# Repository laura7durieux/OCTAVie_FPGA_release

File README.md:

# OCTAVie – Ultrasonic Acquisition Platform

**OCTAVie** is an open-source hardware and software platform designed to capture and analyze ultrasonic vocalizations of animals (up to ≥80 kHz).  
It combines a sensitive microphone module, an analog front-end, an FPGA-based acquisition unit, and a PC application for real-time spectral analysis.

This repository hosts the **complete open-source design files**: electronics, enclosures, FPGA firmware, PC software, documentation, and example datasets.  
The project is developed at **ICube, LNCA, and the Faculty of Physics and Engineering – Strasbourg, France**, within the framework of the **OCTAVie project**.

---

## Quickstart

### 1. Build Hardware
- Go to [hardware/](hardware/)  
- Assemble the **microphone** and the **acquisition unit** following the build guide:  
  - [docs/build_guide/pcb_assembly.md](docs/build_guide/pcb_assembly.md)  
  - [docs/build_guide/mechanical_assembly.md](docs/build_guide/mechanical_assembly.md)  
- Complete system integration: [hardware/system_integration/final_assembly.md](hardware/system_integration/final_assembly.md)

### 2. Program FPGA
- Go to [firmware_fpga/](firmware_fpga/)  
- Compile the project in Quartus (or use provided bitstreams in [releases/](releases/))  
- Load bitstream on Cyclone V GX using Quartus Programmer

### 3. Run PC Application
- Go to [software_pc/](software_pc/)  
- Install dependencies
- Run the software

### Documentation
- Build guide → docs/build_guide/
- User guide → docs/user_guide/user_manual.md
- Validation & tests → docs/validation/
- BOM → docs/publication_assets/tables/bom_master_v1.0.csv

### Citation
If you use this project, please cite the associated HardwareX article and Zenodo DOI:
10.5281/zenodo.17356089

### License
- Hardware → CERN OHL-S v2.0
- Software → GPL-3.0
- Documentation → CC BY-SA 4.0
(see LICENSES/)

---

## Repository Structure
Please see the document : File_list_V1.xlsx 
This document regroups all the documents available in this project as well as their localisation and their status.

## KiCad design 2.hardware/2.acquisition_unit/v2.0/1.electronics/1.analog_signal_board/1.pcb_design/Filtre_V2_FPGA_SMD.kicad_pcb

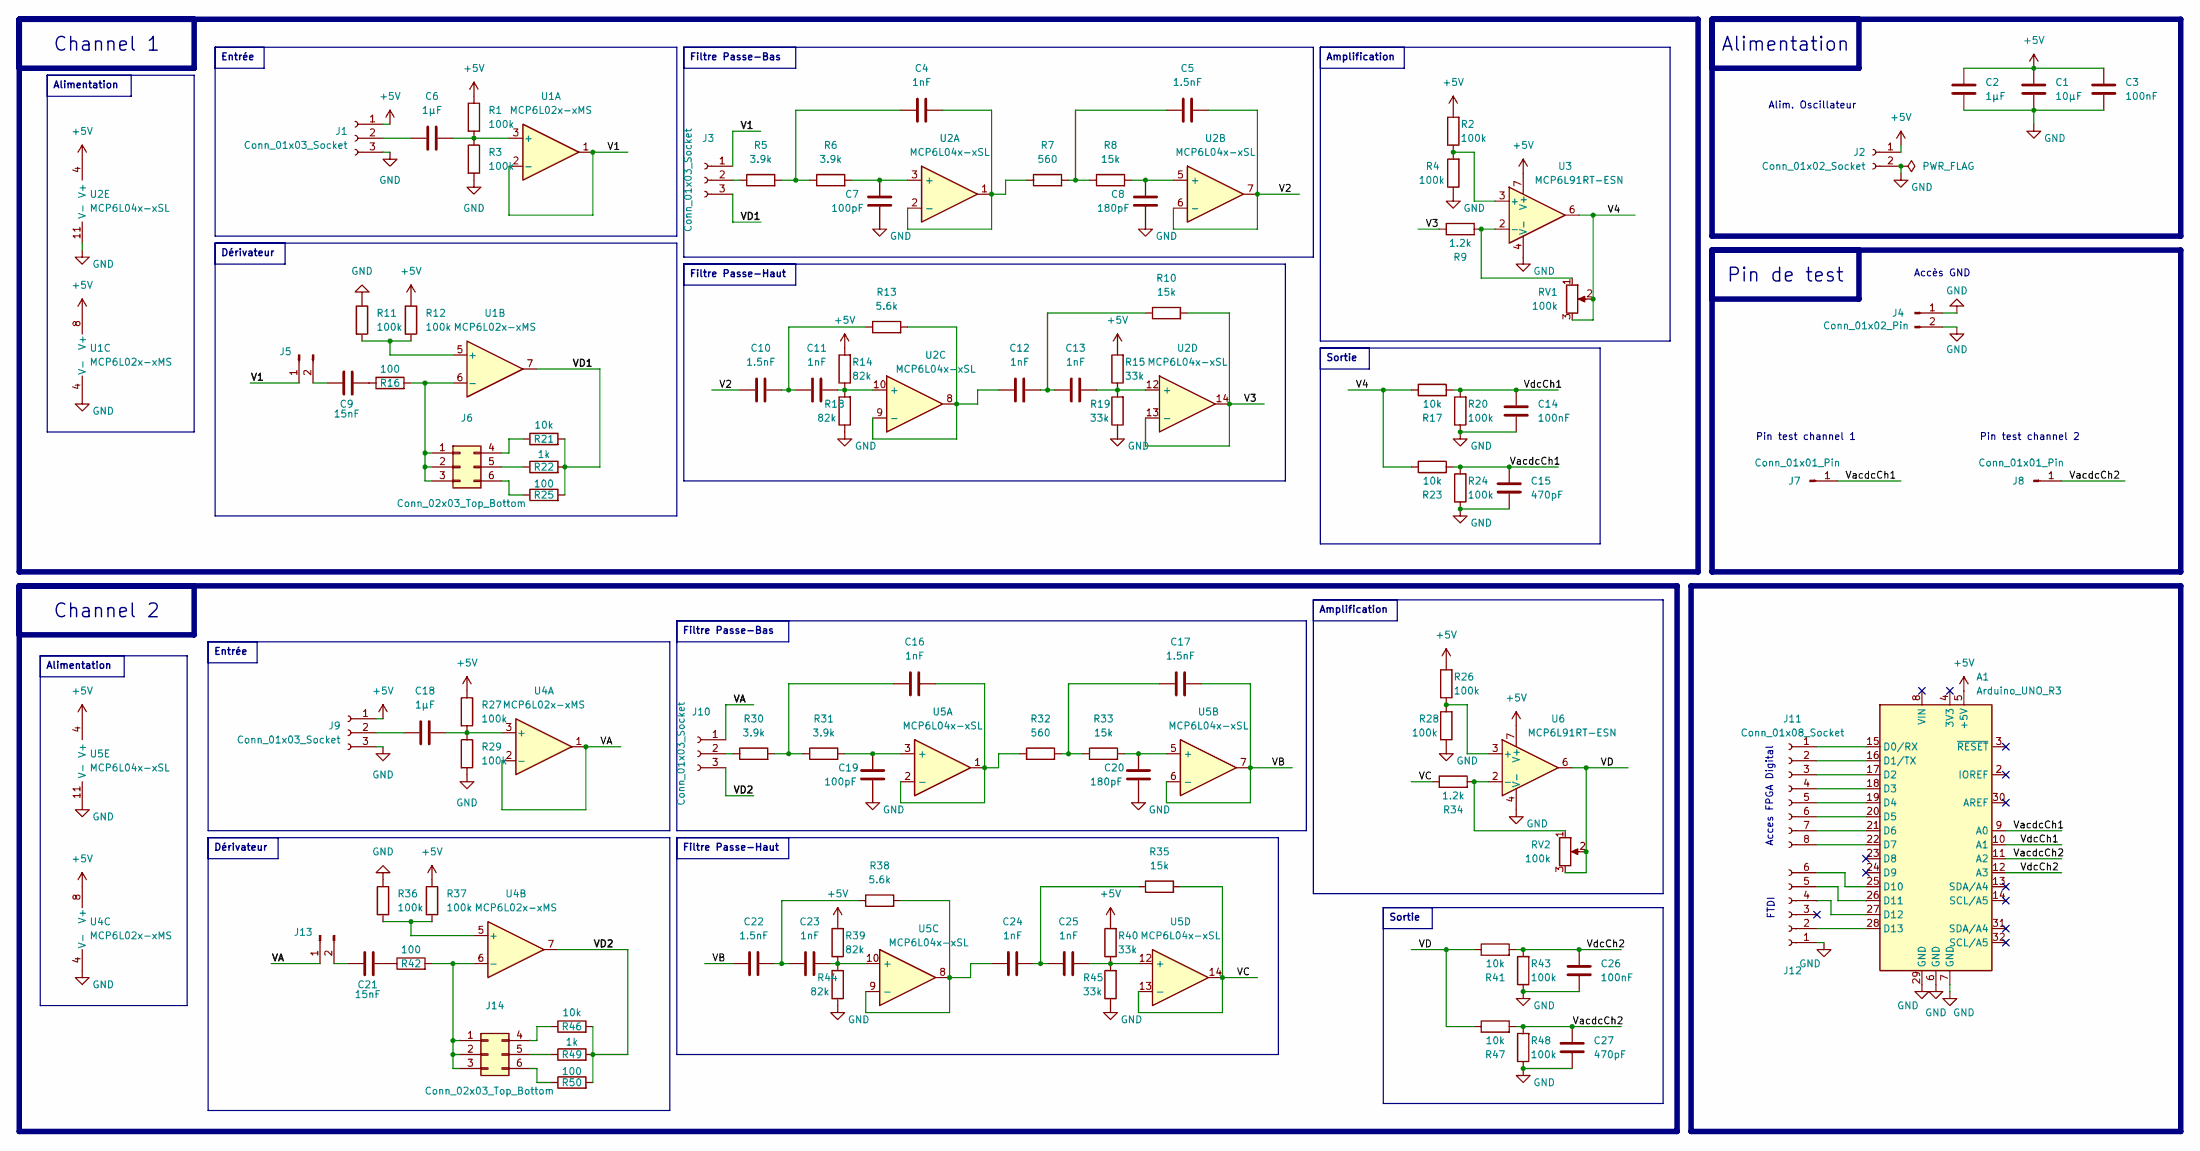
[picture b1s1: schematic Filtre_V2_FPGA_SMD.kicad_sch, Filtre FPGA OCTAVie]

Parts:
A1: Arduino_UNO_R3
C1: 10µF; C_0805_2012Metric; Manufacturer Part Number C0805C106K8PACTU
C2, C6, C18: 1µF; C_0805_2012Metric; Manufacturer Part Number C0805C105K3RAC7800
C3, C14, C26: 100nF; C_0805_2012Metric; Manufacturer Part Number C0805C104M5RAC7800
C4, C11, C12, C13, C16, C23, C24, C25: 1nF; C_0805_2012Metric; Manufacturer Part Number C0805C102K1HAC7800
C5, C10, C17, C22: 1.5nF; C_0805_2012Metric; Manufacturer Part Number C0805C152K3HAC7800
C7, C19: 100pF; C_0805_2012Metric; Manufacturer Part Number C0805C101J5GAC7800
C8, C20: 180pF; C_0805_2012Metric; Manufacturer Part Number C0805C181K5GAC7800
C9, C21: 15nF; C_0805_2012Metric; Manufacturer Part Number C0805C153K5RAC7800
C15, C27: 470pF; C_0805_2012Metric; Manufacturer Part Number C0805C471K5RAC7800
J1, J9: Conn_01x03_Socket; JST_XH_B3B-XH-AM_1x03_P2.50mm_Vertical; Manufacturer Part Number B3B-XH-A
J2: Conn_01x02_Socket; PinHeader_1x02_P2.54mm_Vertical; Manufacturer Part Number PH1-02-UA
J3, J10: Conn_01x03_Socket; PinHeader_1x03_P2.54mm_Vertical; Manufacturer Part Number PH1-03-UA
J4: Conn_01x02_Pin; PinHeader_1x02_P2.54mm_Vertical; Manufacturer Part Number PH1-02-UA
J5, J13: Conn_01x02_Pin; PinSocket_1x02_P2.54mm_Vertical; Manufacturer Part Number PH1-02-UA
J6, J14: Conn_02x03_Top_Bottom; PinHeader_2x03_P2.54mm_Vertical; Manufacturer Part Number PH2-06-UA
J7, J8: Conn_01x01_Pin; PinHeader_1x01_P2.54mm_Vertical; Manufacturer Part Number PH1-01-UA
J11: Conn_01x08_Socket; PinHeader_1x08_P2.54mm_Vertical; Manufacturer Part Number PH1-08-UA
J12: Conn_01x06_Socket; JST_XH_B6B-XH-A_1x06_P2.50mm_Vertical; Manufacturer Part Number B6B-XH-A
R1, R2, R3, R4, R11, R12, R20, R24, R26, R27, R28, R29, R36, R37, R43, R48: 100k; R_0805_2012Metric; Manufacturer Part Number ERJ-P06J104V
R5, R6, R30, R31: 3.9k; R_0805_2012Metric; Manufacturer Part Number ERJ-P06J392V
R7, R32: 560; R_0805_2012Metric; Manufacturer Part Number ERJ-P06J561V
R8, R10, R33, R35: 15k; R_0805_2012Metric; Manufacturer Part Number ERJ-P06J153V
R9, R34: 1.2k; R_0805_2012Metric; Manufacturer Part Number ERJ-P06J122V
R13, R38: 5.6k; R_0805_2012Metric; Manufacturer Part Number ERJ-P06J562V
R14, R18, R39, R44: 82k; R_0805_2012Metric; Manufacturer Part Number ERJ-P06J823V
R15, R19, R40, R45: 33k; R_0805_2012Metric; Manufacturer Part Number ERJ-P06J333V
R16, R25, R42, R50: 100; R_0805_2012Metric; Manufacturer Part Number ERJ-P06J101V
R17, R21, R23, R41, R46, R47: 10k; R_0805_2012Metric; Manufacturer Part Number ERJ-P06J103V
R22, R49: 1k; R_0805_2012Metric; Manufacturer Part Number ERJ-P06J102V
RV1, RV2: 100k; JST_XH_B3B-XH-AM_1x03_P2.50mm_Vertical; Manufacturer Part Number ERJ-P06J104V
U1, U4: MCP6L02x-xMS; SOIC-8_3.9x4.9mm_P1.27mm; Manufacturer Part Number MCP6022T-I/SN
U2, U5: MCP6L04x-xSL; SOIC-14_3.9x8.7mm_P1.27mm; Manufacturer Part Number MCP6024-I/SL
U3, U6: MCP6L91RT-ESN; SOIC-8_3.9x4.9mm_P1.27mm; Manufacturer Part Number MCP6021-I/SN

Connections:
+5V: A1.5 (+5V), C1.1, C2.1, C3.1, J1.1, J2.1, J9.1, R1.1, R2.2, R12.1, R14.2, R15.2, R26.2, R27.1, R37.1, R39.2, R40.2, U1.8 (V+), U2.4 (V+), U3.7 (V+), U4.8 (V+), U5.4 (V+), U6.7 (V+)
/V1: J3.1, J5.1, U1.1, U1.2 (-)
/V2: C5.2, C10.1, U2.6 (-), U2.7
/V3: R9.1, R10.2, U2.13 (-), U2.14
/V4: R17.1, R23.1, RV1.2, RV1.3, U3.6
/VA: J10.1, J13.1, U4.1, U4.2 (-)
/VB: C17.2, C22.1, U5.6 (-), U5.7
/VC: R34.1, R35.2, U5.13 (-), U5.14
/VD: R41.1, R47.1, RV2.2, RV2.3, U6.6
/VD1: J3.3, R21.2, R22.2, R25.2, U1.7
/VD2: J10.3, R46.2, R49.2, R50.2, U4.7
/VacdcCh1: A1.9 (A0), C15.2, J7.1, R23.2, R24.2
/VacdcCh2: A1.11 (A2), C27.2, J8.1, R47.2, R48.2
/VdcCh1: A1.10 (A1), C14.2, R17.2, R20.2
/VdcCh2: A1.12 (A3), C26.2, R41.2, R43.2
GND: A1.6 (GND), A1.7 (GND), A1.29 (GND), C1.2, C2.2, C3.2, C7.1, C8.1, C14.1, C15.1, C19.1, C20.1, C26.1, C27.1, J1.3, J2.2, J4.1, J4.2, J9.3, J12.1, R3.2, R4.1, R11.1, R18.1, R19.1, R20.1, R24.1, R28.1, R29.2, R36.1, R43.1, R44.1, R45.1, R48.1, U1.4 (V-), U2.11 (V-), U3.4 (V-), U4.4 (V-), U5.11 (V-), U6.4 (V-)
unnamed: A1.15 (D0/RX), J11.1
unnamed: A1.16 (D1/TX), J11.2
unnamed: A1.17 (D2), J11.3
unnamed: A1.18 (D3), J11.4
unnamed: A1.19 (D4), J11.5
unnamed: A1.20 (D5), J11.6
unnamed: A1.21 (D6), J11.7
unnamed: A1.22 (D7), J11.8
unnamed: A1.25 (D10), J12.6
unnamed: A1.26 (D11), J12.5
unnamed: A1.27 (D12), J12.4
unnamed: A1.28 (D13), J12.2
unnamed: C4.1, R5.2, R6.1
unnamed: C5.1, R7.2, R8.1
unnamed: C9.2, R16.1
unnamed: C10.2, C11.1, R13.1
unnamed: C12.2, C13.1, R10.1
unnamed: C16.1, R30.2, R31.1
unnamed: C17.1, R32.2, R33.1
unnamed: C21.2, R42.1
unnamed: C22.2, C23.1, R38.1
unnamed: C24.2, C25.1, R35.1
unnamed: C6.1, J1.2
unnamed: J3.2, R5.1
unnamed: C9.1, J5.2
unnamed: J6.1, J6.2, J6.3, R16.2, U1.6 (-)
unnamed: J6.4, R21.1
unnamed: J6.5, R22.1
unnamed: J6.6, R25.1
unnamed: C18.1, J9.2
unnamed: J10.2, R30.1
unnamed: C21.1, J13.2
unnamed: J14.1, J14.2, J14.3, R42.2, U4.6 (-)
unnamed: J14.4, R46.1
unnamed: J14.5, R49.1
unnamed: J14.6, R50.1
unnamed: C6.2, R1.2, R3.1, U1.3 (+)
unnamed: R11.2, R12.2, U1.5 (+)
unnamed: C7.2, R6.2, U2.3 (+)
unnamed: C4.2, R7.1, U2.1, U2.2 (-)
unnamed: C8.2, R8.2, U2.5 (+)
unnamed: C11.2, R14.1, R18.2, U2.10 (+)
unnamed: C12.1, R13.2, U2.8, U2.9 (-)
unnamed: C13.2, R15.1, R19.2, U2.12 (+)
unnamed: R2.1, R4.2, U3.3 (+)
unnamed: R9.2, RV1.1, U3.2 (-)
unnamed: C18.2, R27.2, R29.1, U4.3 (+)
unnamed: R36.2, R37.2, U4.5 (+)
unnamed: C19.2, R31.2, U5.3 (+)
unnamed: C16.2, R32.1, U5.1, U5.2 (-)
unnamed: C20.2, R33.2, U5.5 (+)
unnamed: C23.2, R39.1, R44.2, U5.10 (+)
unnamed: C24.1, R38.2, U5.8, U5.9 (-)
unnamed: C25.2, R40.1, R45.2, U5.12 (+)
unnamed: R26.1, R28.2, U6.3 (+)
unnamed: R34.2, RV2.1, U6.2 (-)

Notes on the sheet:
Alim. Oscillateur
FTDI
Pin test channel 1
Accès GND
Acces FPGA Digital
Pin test channel 2
Alimentation
Filtre Passe-Bas
Dérivateur
Entrée
Amplification
Filtre Passe-Haut
Channel 2
Channel 1
Sortie
Pin de test

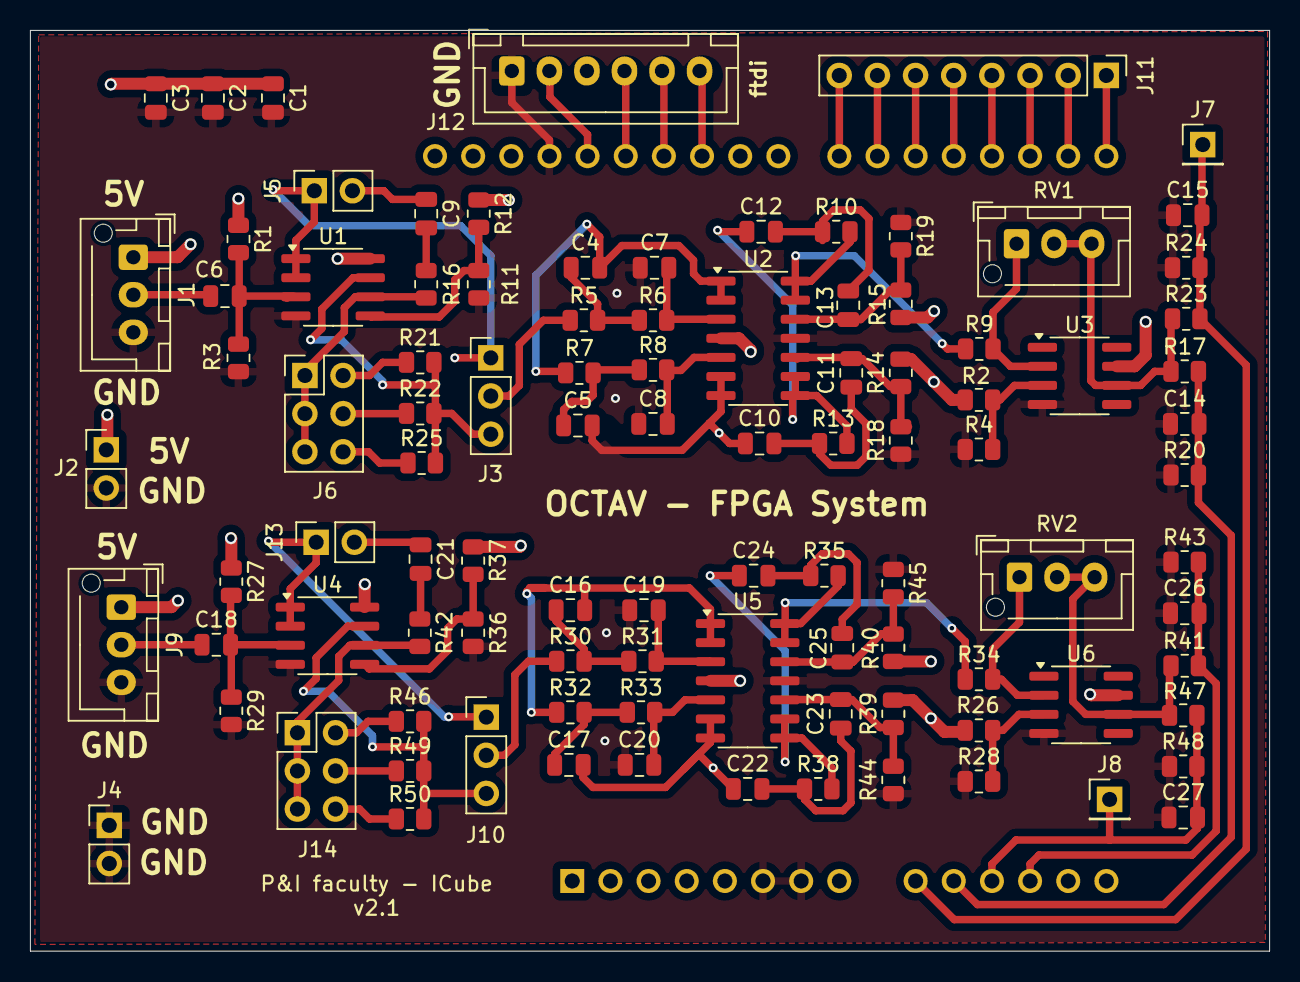
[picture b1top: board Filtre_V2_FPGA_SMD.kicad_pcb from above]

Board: 4 copper layers, 82.5 x 61.3 mm, 100 parts (1 on the bottom side), 72 nets.

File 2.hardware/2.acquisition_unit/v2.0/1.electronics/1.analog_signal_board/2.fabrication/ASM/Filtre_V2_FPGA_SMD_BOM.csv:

"","Sourced","Placed","References","Value","Footprint","Quantity"
1,"","","C4, C11, C12, C13, C16, C23, C24, C25","1nF","C_0805_2012Metric",8
2,"","","C5, C10, C17, C22","1.5nF","C_0805_2012Metric",4
3,"","","C2, C6, C18","1µF","C_0805_2012Metric",3
4,"","","C3, C14, C26","100nF","C_0805_2012Metric",3
5,"","","C7, C19","100pF","C_0805_2012Metric",2
6,"","","C8, C20","180pF","C_0805_2012Metric",2
7,"","","C9, C21","15nF","C_0805_2012Metric",2
8,"","","C15, C27","470pF","C_0805_2012Metric",2
9,"","","C1","10µF","C_0805_2012Metric",1
10,"","","R1, R2, R3, R4, R11, R12, R20, R24, R26, R27, R28, R29, R36, R37, R43, R48, RV1, RV2","100k","R_0805_2012Metric, JST_XH_B3B-XH-AM_1x03_P2.50mm_Vertical",18
11,"","","R17, R21, R23, R41, R46, R47","10k","R_0805_2012Metric",6
12,"","","R5, R6, R30, R31","3.9k","R_0805_2012Metric",4
13,"","","R8, R10, R33, R35","15k","R_0805_2012Metric",4
14,"","","R14, R18, R39, R44","82k","R_0805_2012Metric",4
15,"","","R15, R19, R40, R45","33k","R_0805_2012Metric",4
16,"","","R16, R25, R42, R50",100,"R_0805_2012Metric",4
17,"","","R7, R32",560,"R_0805_2012Metric",2
18,"","","R9, R34","1.2k","R_0805_2012Metric",2
19,"","","R13, R38","5.6k","R_0805_2012Metric",2
20,"","","R22, R49","1k","R_0805_2012Metric",2
21,"","","U1, U4","MCP6L02x-xMS","SOIC-8_3.9x4.9mm_P1.27mm",2
22,"","","U2, U5","MCP6L04x-xSL","SOIC-14_3.9x8.7mm_P1.27mm",2
23,"","","U3, U6","MCP6L91RT-ESN","SOIC-8_3.9x4.9mm_P1.27mm",2
24,"","","A1","Arduino_UNO_R3","Arduino_UNO_R3",1
25,"","","J1, J3, J9, J10","Conn_01x03_Socket","JST_XH_B3B-XH-AM_1x03_P2.50mm_Vertical, PinHeader_1x03_P2.54mm_Vertical",4
26,"","","J4, J5, J13","Conn_01x02_Pin","PinHeader_1x02_P2.54mm_Vertical, PinSocket_1x02_P2.54mm_Vertical",3
27,"","","J6, J14","Conn_02x03_Top_Bottom","PinHeader_2x03_P2.54mm_Vertical",2
28,"","","J7, J8","Conn_01x01_Pin","PinHeader_1x01_P2.54mm_Vertical",2
29,"","","J2","Conn_01x02_Socket","PinHeader_1x02_P2.54mm_Vertical",1
30,"","","J11","Conn_01x08_Socket","PinHeader_1x08_P2.54mm_Vertical",1
31,"","","J12","Conn_01x06_Socket","PinHeader_1x06_P2.54mm_Vertical",1

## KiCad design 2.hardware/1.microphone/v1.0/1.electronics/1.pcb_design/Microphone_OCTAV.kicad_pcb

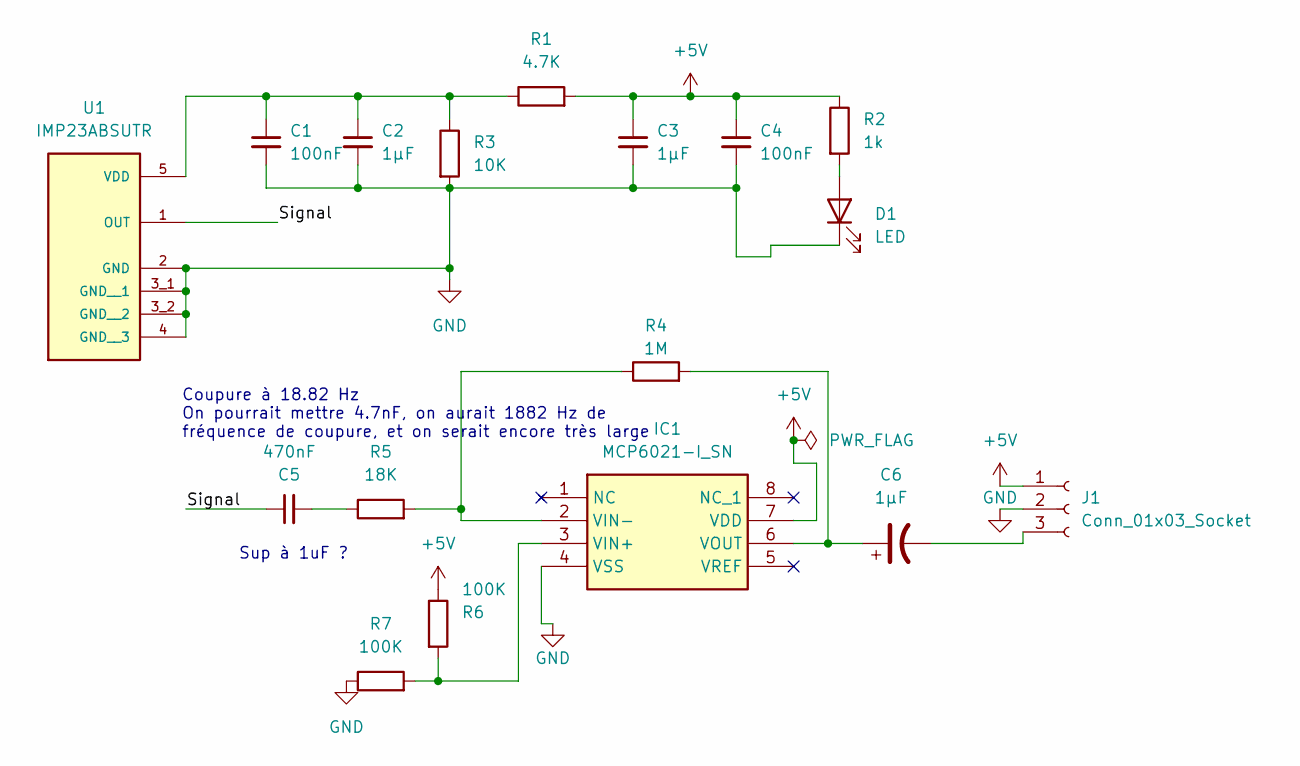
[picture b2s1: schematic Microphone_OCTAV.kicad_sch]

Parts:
C1, C4: 100nF; C_0805_2012Metric; Manufacturer_Part_Number C0805C104K5RACTU
C2, C3, C6: 1µF; C_0805_2012Metric; Manufacturer_Part_Number C0805C105K3RACTU
C5: 470nF; C_0805_2012Metric; Manufacturer_Part_Number C0805C474K5RACTU
D1: LED; LED_0805_2012Metric; Manufacturer_Part_Number 150080RS75000
IC1: MCP6021-I_SN; SOIC127P600X175-8N; Mouser Part Number 579-MCP6021-I/SN
J1: Conn_01x03_Socket; CONN_B3B-PH-SM4-TB_03P_JST; Manufacturer_Part_Number B3B-PH-SM4-TB
R1: 4.7K; R_0805_2012Metric; Manufacturer_Part_Number AC0805FR-074K7L
R2: 1k; R_0805_2012Metric; Manufacturer_Part_Number RC0805JR-071KL
R3: 10K; R_0805_2012Metric; Manufacturer_Part_Number RC0805JR-0710KL
R4: 1M; R_0805_2012Metric; Manufacturer_Part_Number RC0805JR-071ML
R5: 18K; R_0805_2012Metric; Manufacturer_Part_Number RC0805JR-0718KL
R6, R7: 100K; R_0805_2012Metric; Manufacturer_Part_Number RC0805JR-07100KL
U1: IMP23ABSUTR; MIC_IMP23ABSUTR; PARTREV 2

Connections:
+5V: C3.1, C4.1, IC1.7 (VDD), J1.1, R1.2, R2.1, R6.1
/Signal: C5.1, U1.1 (OUT)
GND: C1.2, C2.2, C3.2, C4.2, D1.1 (K), IC1.4 (VSS), J1.2, R3.2, R7.1, U1.2 (GND), U1.3_1 (GND__1), U1.3_2 (GND__2), U1.4 (GND__3)
unnamed: C5.2, R5.1
unnamed: D1.2 (A), R2.2
unnamed: IC1.3 (VIN+), R6.2, R7.2
unnamed: IC1.2 (VIN-), R4.1, R5.2
unnamed: C6.1, IC1.6 (VOUT), R4.2
unnamed: C6.2, J1.3
unnamed: C1.1, C2.1, R1.1, R3.1, U1.5 (VDD)

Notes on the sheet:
Sup à 1uF ?
Coupure à 18.82 Hz On pourrait mettre 4.7nF, on aurait 1882 Hz de fréquence de coupure, et on serait encore très large

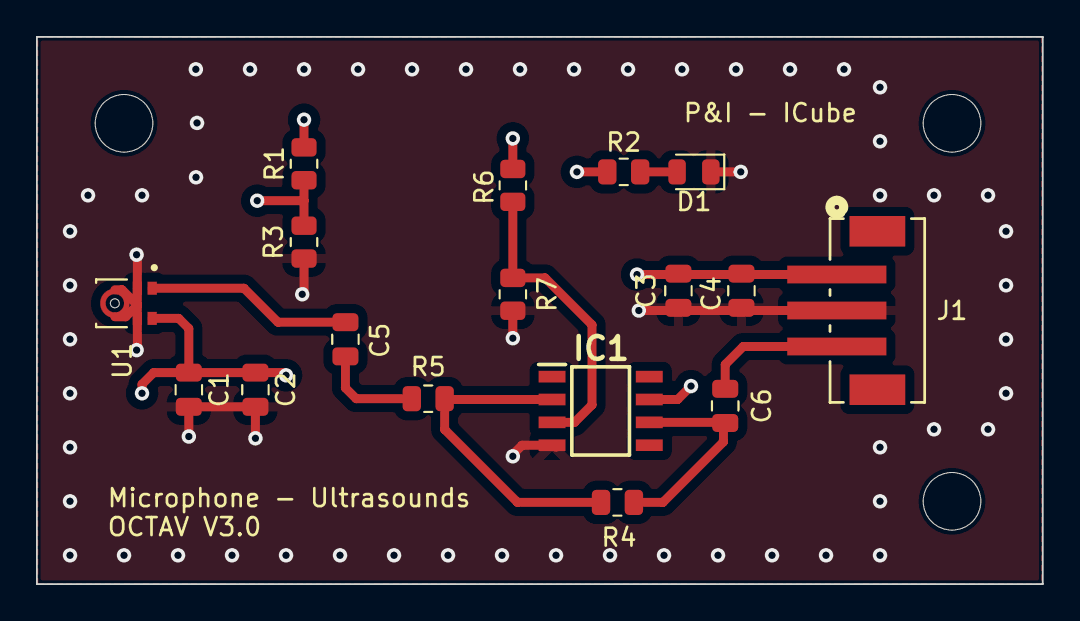
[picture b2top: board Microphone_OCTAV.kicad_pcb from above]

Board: 4 copper layers, 55.9 x 30.4 mm, 17 parts (0 on the bottom side), 10 nets.

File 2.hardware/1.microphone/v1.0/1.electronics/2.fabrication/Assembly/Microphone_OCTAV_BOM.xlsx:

Designator | Qty | Value | MN | MP
C1,C4 | 2 | 100nF | KEMET | C0805C104K5RACTU
C2,C3,C6 | 3 | 1µF | KEMET | C0805C105K3RACTU
C5 | 1 | 470nF | KEMET | C0805C474K5RACTU
D1 | 1 | 150080RS75000 | Wurth Elektronik | 150080RS75000
IC1 | 1 | MCP6021-I_SN | Microchip | MCP6021-I/SN
J1 | 1 | B3B-PH-SM4-TB | JST Sales America Inc. | B3B-PH-SM4-TB
R1 | 1 | 4.7K | YAGEO | AC0805FR-074K7L
R2 | 1 | 1k | YAGEO | RC0805JR-071KL
R3 | 1 | 10K | YAGEO | RC0805JR-0710KL
R4 | 1 | 1M | YAGEO | RC0805JR-071ML
R5 | 1 | 18K | YAGEO | RC0805JR-0718KL
R6,R7 | 2 | 100K | YAGEO | RC0805JR-07100KL
U1 | 1 | IMP23ABSUTR | STMicroelectronics | IMP23ABSUTR

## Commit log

2025-10-12 Build microphone tutorial add up
2025-10-25 udapte docs
2025-10-29 Update VHDL
    Update comments on vhdl file + Writing the schematic doc explanation
2025-11-01 General Review
